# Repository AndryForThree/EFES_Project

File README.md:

# EFES_Project
Final Project for "Electronics for Embedded Systems" course of PoliTO 2026-2027. Automotive Steering System 

## File versionati e rigenerazione

Le regole sono commentate in `.gitignore`, `Firmware/.gitignore` e nel
`.gitignore` del firmware HumanSide.

- **KiCad:** schemi, PCB, progetti, regole e librerie (inclusi i modelli 3D).
  History locali, backup, lock, preferenze `.kicad_prl`, PDF e Gerber sono esclusi.
- **FreeCAD:** macro, script, JSON e documenti `.FCStd`; STEP/STL in `CAD/`
  e anteprime generate sono esclusi. Rigenerarli eseguendo le macro FreeCAD.
  I modelli in `PCB/CustomLibs/3D/` sono invece dipendenze del progetto KiCad.
- **Quartus/ModelSim:** HDL, testbench, script, `.qpf`, `.qsf`, IP e vincoli;
  database, prodotti di compilazione e simulazione sono esclusi.
- **STM32CubeMX/CMake:** `.ioc`, codice custom e configurazioni manuali;
  SDK, scaffolding rigenerabile e prodotti di build sono esclusi.
  Per HumanSide seguire `Firmware/EFES_FW_HumanSide/README.md`.
  Prima di compilare rigenerare anche font e asset con
  `python3 generate_font.py` in `Firmware/Scripts/FontGeneration/` e
  `python3 generate_assets.py` in `Firmware/Scripts/SymbolsGeneration/`.
- **Python:** sorgenti, test, configurazioni e dipendenze; ambienti virtuali,
  cache e prodotti di packaging sono esclusi.
- **LaTeX:** `.tex`, bibliografie e figure; file intermedi e PDF compilati
  dei report sono esclusi. Datasheet, riferimenti e allegati restano versionati.

I file ignorati restano disponibili sul disco ma non entrano nei commit.

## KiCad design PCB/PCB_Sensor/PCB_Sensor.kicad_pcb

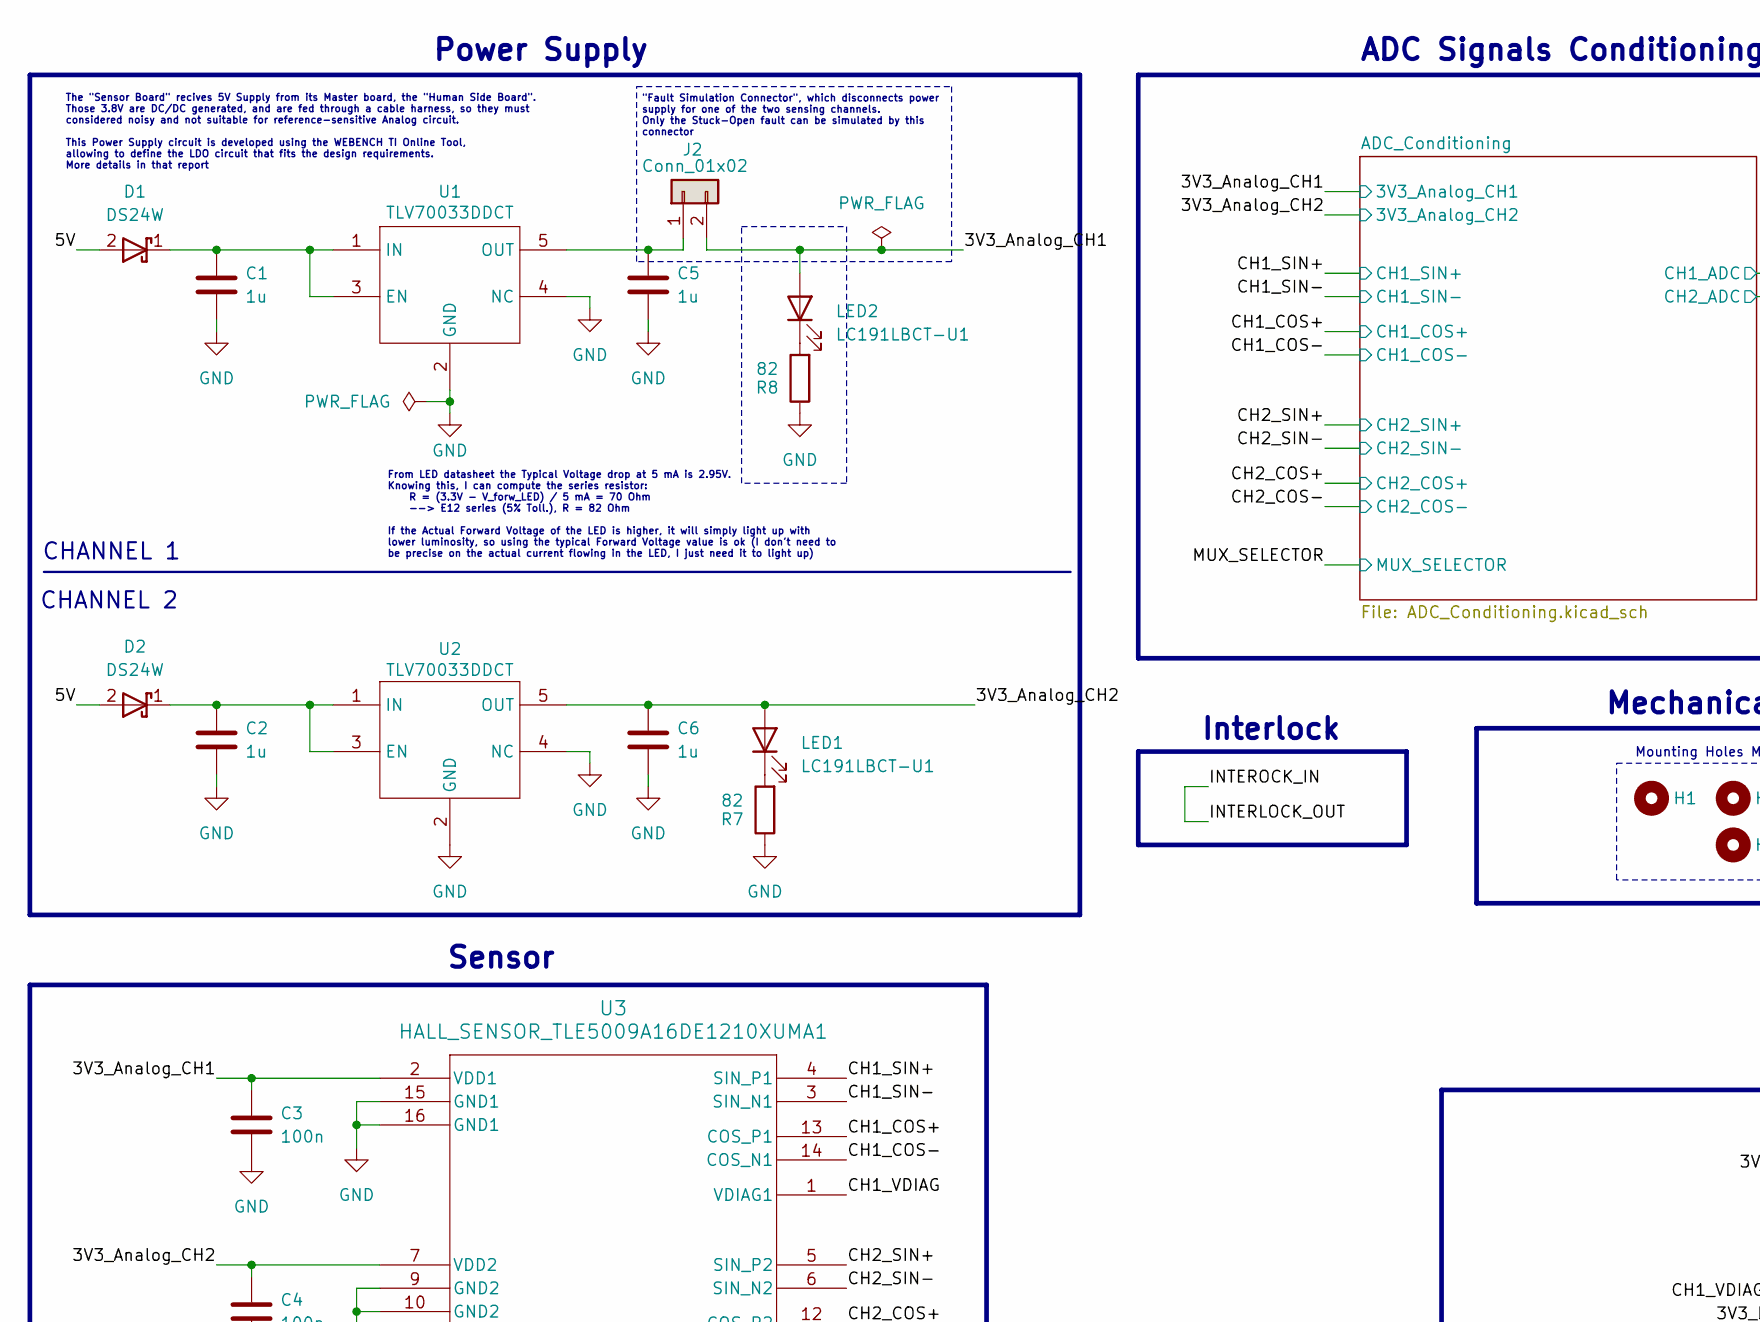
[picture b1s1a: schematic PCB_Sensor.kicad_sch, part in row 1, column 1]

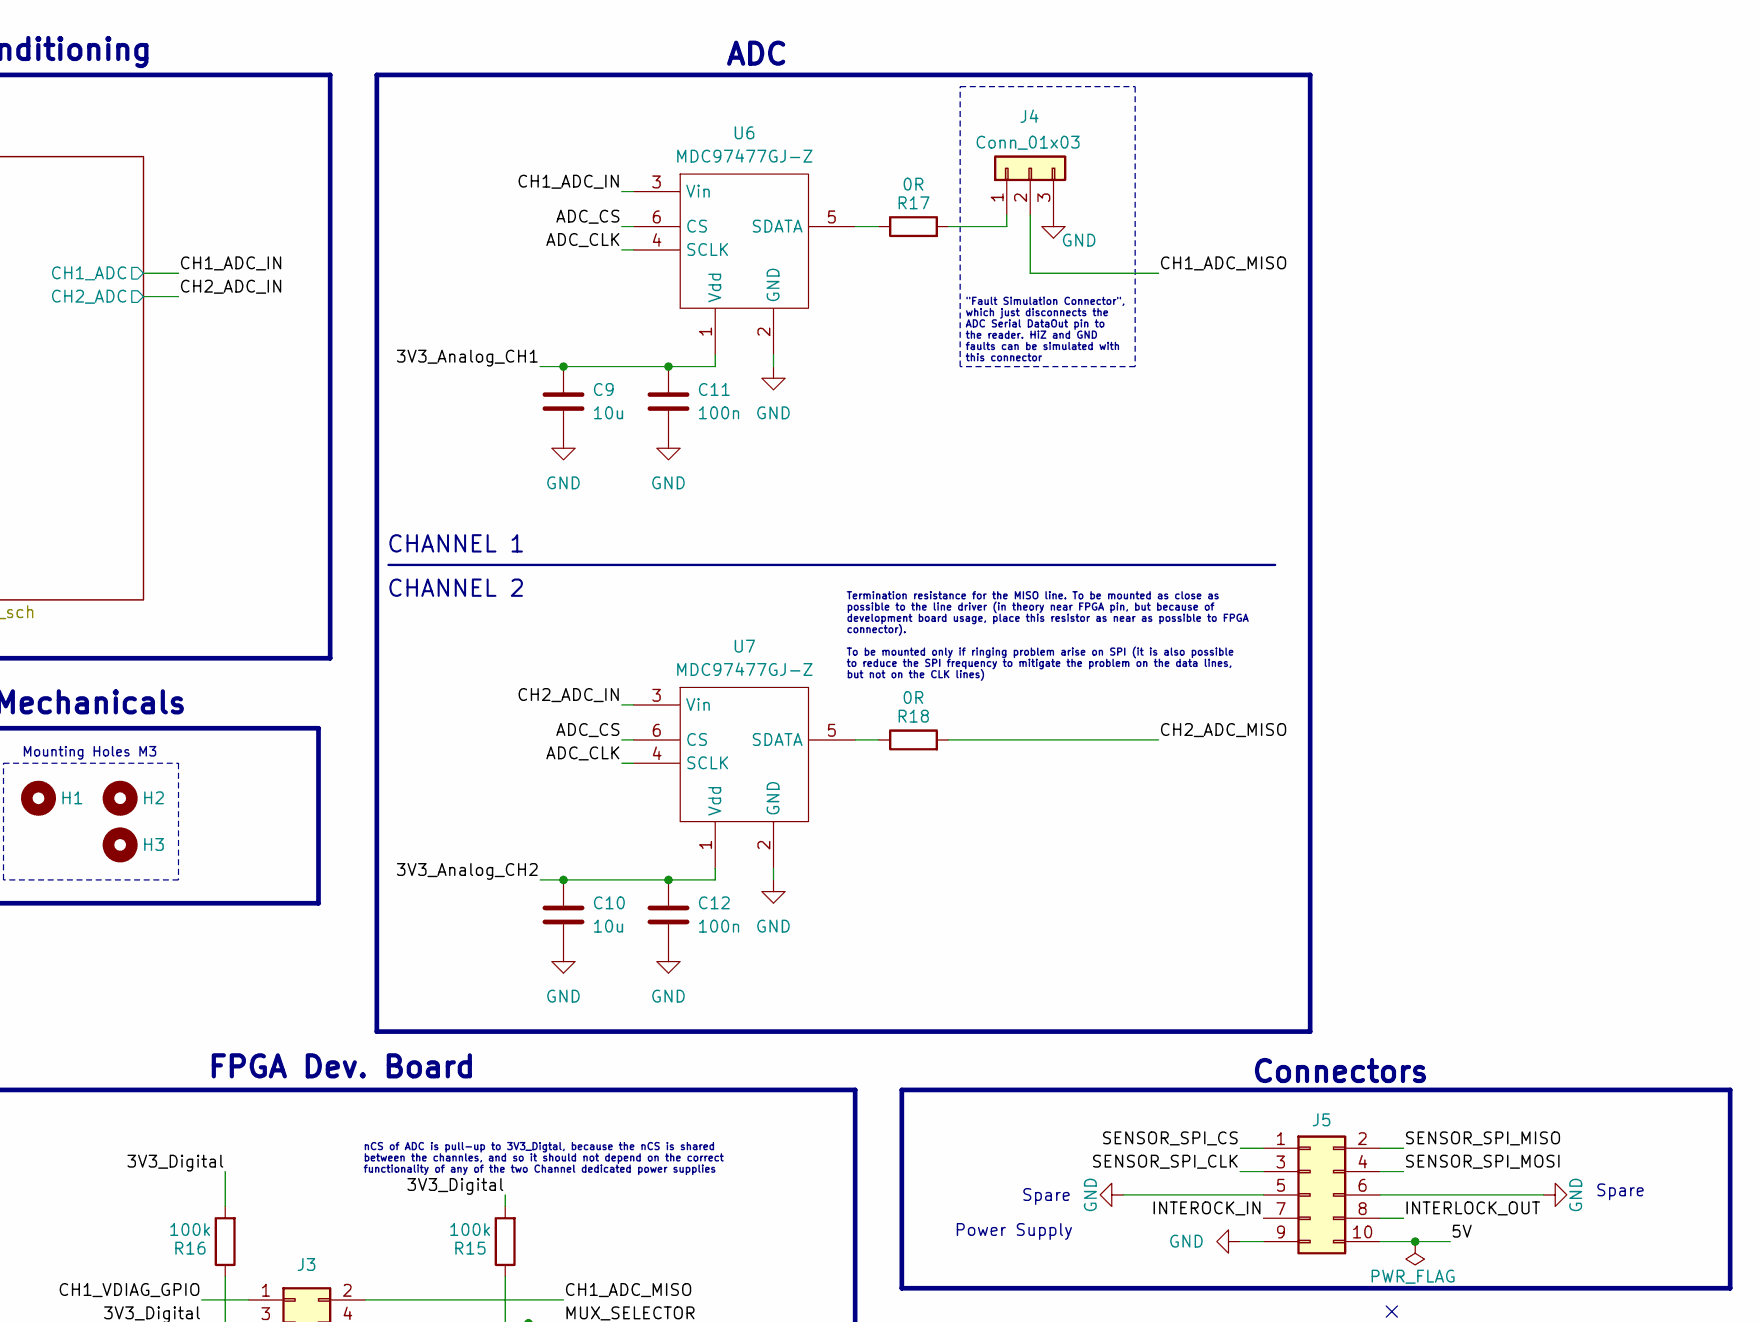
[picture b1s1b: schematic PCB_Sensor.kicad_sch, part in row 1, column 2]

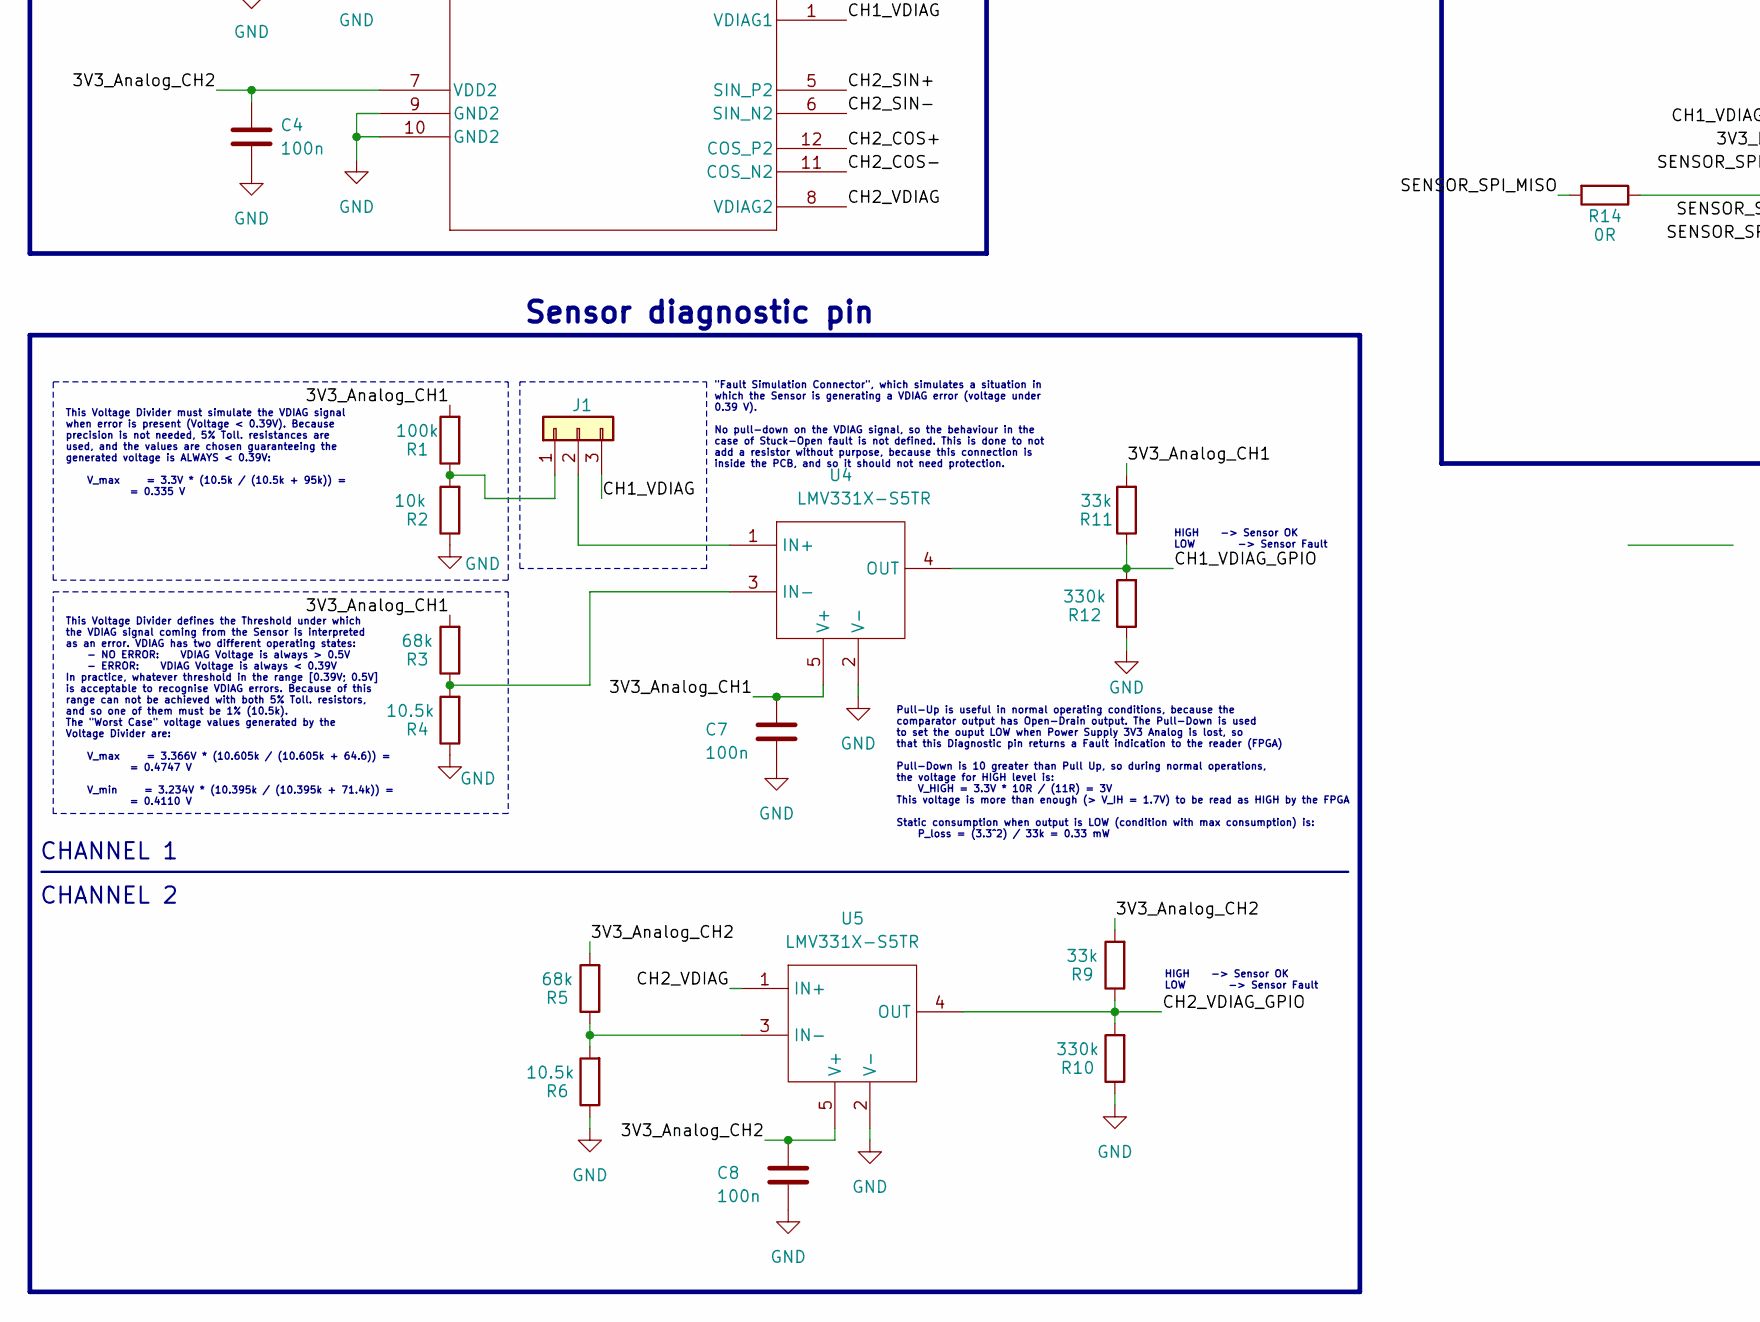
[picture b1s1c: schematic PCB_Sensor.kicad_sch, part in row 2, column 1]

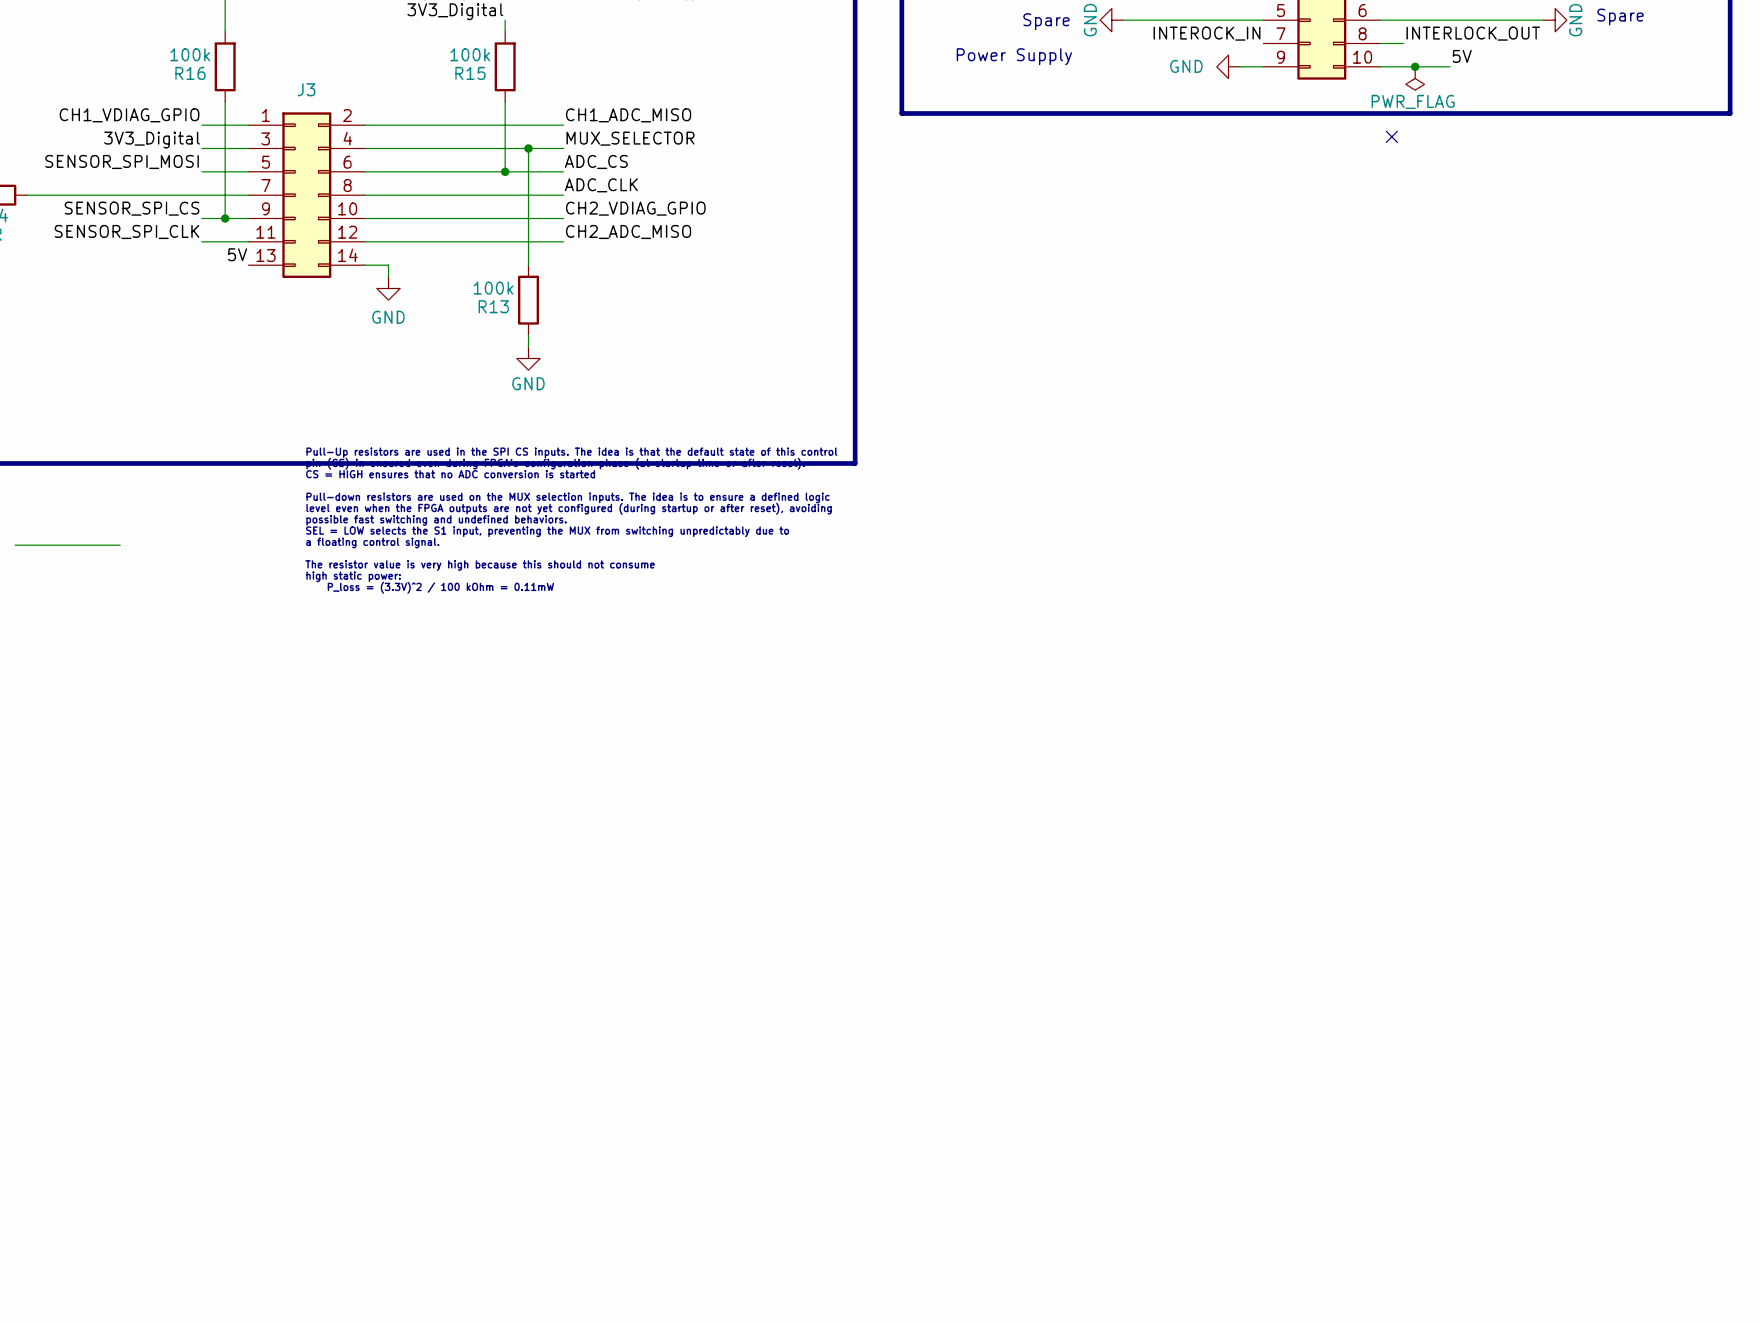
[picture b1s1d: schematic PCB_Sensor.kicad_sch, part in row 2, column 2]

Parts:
C1, C2, C5, C6: 1u; C_0805_2012Metric_Pad1.18x1.45mm_HandSolder
C3, C4, C7, C8, C11, C12: 100n; C_0805_2012Metric_Pad1.18x1.45mm_HandSolder
C9, C10: 10u; C_0805_2012Metric_Pad1.18x1.45mm_HandSolder
D1, D2: DS24W; SOD-123_HandSolder
H1, H2, H3: MountingHole; MountingHole_3.2mm_M3
J1, J4: Conn_01x03; PinHeader_1x03_P2.54mm_Vertical
J2: Conn_01x02; PinHeader_1x02_P2.54mm_Vertical
J3: SBH11-PBPC-D07-ST-BK; CONN_SBH11-PBPC-D07-ST-BK
J5: SBH11-PBPC-D05-RA-BK; CONN_SBH11-PBPC-D05-RA-BK
LED1, LED2: LC191LBCT-U1; LED_0603_HandSolder
R1, R13, R15, R16: 100k; R_0805_2012Metric_Pad1.20x1.40mm_HandSolder
R2: 10k; R_0805_2012Metric_Pad1.20x1.40mm_HandSolder
R3, R5: 68k; R_0805_2012Metric_Pad1.20x1.40mm_HandSolder
R4, R6: 10.5k; R_0805_2012Metric_Pad1.20x1.40mm_HandSolder
R7, R8: 82; R_0805_2012Metric_Pad1.20x1.40mm_HandSolder
R9, R11: 33k; R_0805_2012Metric_Pad1.20x1.40mm_HandSolder
R10, R12: 330k; R_0805_2012Metric_Pad1.20x1.40mm_HandSolder
R14, R17, R18: 0R; R_0805_2012Metric_Pad1.20x1.40mm_HandSolder
U1, U2: TLV70033DDCT; SOT-23-5
U3: HALL_SENSOR_TLE5009A16DE1210XUMA1
U4, U5: LMV331X-S5TR; SOT-23-5
U6, U7: MDC97477GJ-Z; SOT-23-6_DBV_TEX-M

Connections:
/3V3_Analog_CH1: C3.1, C7.1, C9.1, C11.1, J2.2, LED2.2 (A), R1.2, R3.2, R11.2, U3.2 (VDD1), U4.5 (V+), U6.1 (Vdd); also elsewhere on the board
/3V3_Analog_CH2: C4.1, C6.1, C8.1, C10.1, C12.1, LED1.2 (A), R5.2, R9.2, U2.5 (OUT), U3.7 (VDD2), U5.5 (V+), U7.1 (Vdd); also elsewhere on the board
/3V3_Digital: J3.3, R15.2, R16.2
/5V: D1.2 (A), D2.2 (A), J3.13 (Pin_9), J5.10
/ADC_CLK: J3.8, U6.4 (SCLK), U7.4 (SCLK)
/ADC_CS: J3.6, R15.1, U6.6 (CS), U7.6 (CS)
/CH1_ADC_IN: U6.3 (Vin); also elsewhere on the board
/CH1_ADC_MISO: J3.2, J4.2
/CH1_COS+: U3.13 (COS_P1); also elsewhere on the board
/CH1_COS-: U3.14 (COS_N1); also elsewhere on the board
/CH1_SIN+: U3.4 (SIN_P1); also elsewhere on the board
/CH1_SIN-: U3.3 (SIN_N1); also elsewhere on the board
/CH1_VDIAG: J1.3, U3.1 (VDIAG1)
/CH1_VDIAG_GPIO: J3.1, R11.1, R12.2, U4.4 (OUT)
/CH2_ADC_IN: U7.3 (Vin); also elsewhere on the board
/CH2_ADC_MISO: J3.12 (Pin_10), R18.2
/CH2_COS+: U3.12 (COS_P2); also elsewhere on the board
/CH2_COS-: U3.11 (COS_N2); also elsewhere on the board
/CH2_SIN+: U3.5 (SIN_P2); also elsewhere on the board
/CH2_SIN-: U3.6 (SIN_N2); also elsewhere on the board
/CH2_VDIAG: U3.8 (VDIAG2), U5.1 (IN+)
/CH2_VDIAG_GPIO: J3.10, R9.1, R10.2, U5.4 (OUT)
/INTERLOCK_OUT: J5.7, J5.8
/MUX_SELECTOR: J3.4, R13.2; also elsewhere on the board
/SENSOR_SPI_CLK: J3.11 (Pin_9), J5.3
/SENSOR_SPI_CS: J3.9, J5.1, R16.1
/SENSOR_SPI_MISO: J5.2, R14.2
/SENSOR_SPI_MOSI: J3.5, J5.4
GND: C1.2, C2.2, C3.2, C4.2, C5.2, C6.2, C7.2, C8.2, C9.2, C10.2, C11.2, C12.2, J3.14 (Pin_10), J4.3, J5.5, J5.6, J5.9, R2.1, R4.1, R6.1, R7.1, R8.1, R10.1, R12.1, R13.1, U1.2 (GND), U1.4 (NC), U2.2 (GND), U2.4 (NC), U3.9 (GND2), U3.10 (GND2), U3.15 (GND1), U3.16 (GND1), U4.2 (V-), U5.2 (V-), U6.2 (GND), U7.2 (GND); also elsewhere on the board
unnamed: C1.1, D1.1 (K), U1.1 (IN), U1.3 (EN)
unnamed: C2.1, D2.1 (K), U2.1 (IN), U2.3 (EN)
unnamed: J1.1, R1.1, R2.2
unnamed: J1.2, U4.1 (IN+)
unnamed: C5.1, J2.1, U1.5 (OUT)
unnamed: J3.7, R14.1
unnamed: J4.1, R17.2
unnamed: LED1.1 (K), R7.2
unnamed: LED2.1 (K), R8.2
unnamed: R3.1, R4.2, U4.3 (IN-)
unnamed: R5.1, R6.2, U5.3 (IN-)
unnamed: R17.1, U6.5 (SDATA)
unnamed: R18.1, U7.5 (SDATA)

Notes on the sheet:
CHANNEL 2
CHANNEL 1
From LED datasheet the Typical Voltage drop at 5 mA is 2.95V. Knowing this, I can compute the series resistor: R = (3.3V - V_forw_LED) / 5 mA = 70 Ohm --> E12 series (5% Toll.), R = 82 Ohm If the Actual Forward Voltage of the LED is higher, it will simply light up with lower luminosity, so using th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
Spare
Pull-Up is useful in normal operating conditions, because the comparator output has Open-Drain output. The Pull-Down is used to set the ouput LOW when Power Supply 3V3 Analog is lost, so that this Diagnostic pin returns a Fault indication to the reader (FPGA) Pull-Down is 10 greater than Pull Up, s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
Connectors
"Fault Simulation Connector", which just disconnects the ADC Serial DataOut pin to the reader. HiZ and GND faults can be simulated with this connector
nCS of ADC is pull-up to 3V3_Digtal, because the nCS is shared between the channles, and so it should not depend on the correct functionality of any of the two Channel dedicated power supplies
Sensor diagnostic pin
FPGA Dev. Board
HIGH -> Sensor OK LOW -> Sensor Fault
Mechanicals
Power Supply
ADC Signals Conditioning
This Voltage Divider defines the Threshold under which the VDIAG signal coming from the Sensor is interpreted as an error. VDIAG has two different operating states: - NO ERROR: VDIAG Voltage is always > 0.5V - ERROR: VDIAG Voltage is always < 0.39V In practice, whatever threshold in the range [0.39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
Mounting Holes M3
"Fault Simulation Connector", which simulates a situation in which the Sensor is generating a VDIAG error (voltage under 0.39 V). No pull-down on the VDIAG signal, so the behaviour in the case of Stuck-Open fault is not defined. This is done to not add a resistor without purpose, because this conne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
"Fault Simulation Connector", which disconnects power supply for one of the two sensing channels. Only the Stuck-Open fault can be simulated by this connector
Pull-Up resistors are used in the SPI CS inputs. The idea is that the default state of this control pin (CS) in ensured even during FPGA's configuration phase (at startup time or after reset). CS = HIGH ensures that no ADC conversion is started Pull-down resistors are used on the MUX selection inpu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
Interlock
Termination resistance for the MISO line. To be mounted as close as possible to the line driver (in theory near FPGA pin, but because of development board usage, place this resistor as near as possible to FPGA connector). To be mounted only if ringing problem arise on SPI (it is also possible to re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
Sensor
This Voltage Divider must simulate the VDIAG signal when error is present (Voltage < 0.39V). Because precision is not needed, 5% Toll. resistances are used, and the values are chosen guaranteeing the generated voltage is ALWAYS < 0.39V: V_max = 3.3V * (10.5k / (10.5k + 95k)) = = 0.335 V
ADC
The "Sensor Board" recives 5V Supply from its Master board, the "Human Side Board". Those 3.8V are DC/DC generated, and are fed through a cable harness, so they must considered noisy and not suitable for reference-sensitive Analog circuit. This Power Supply circuit is developed using the WEBENCH TI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

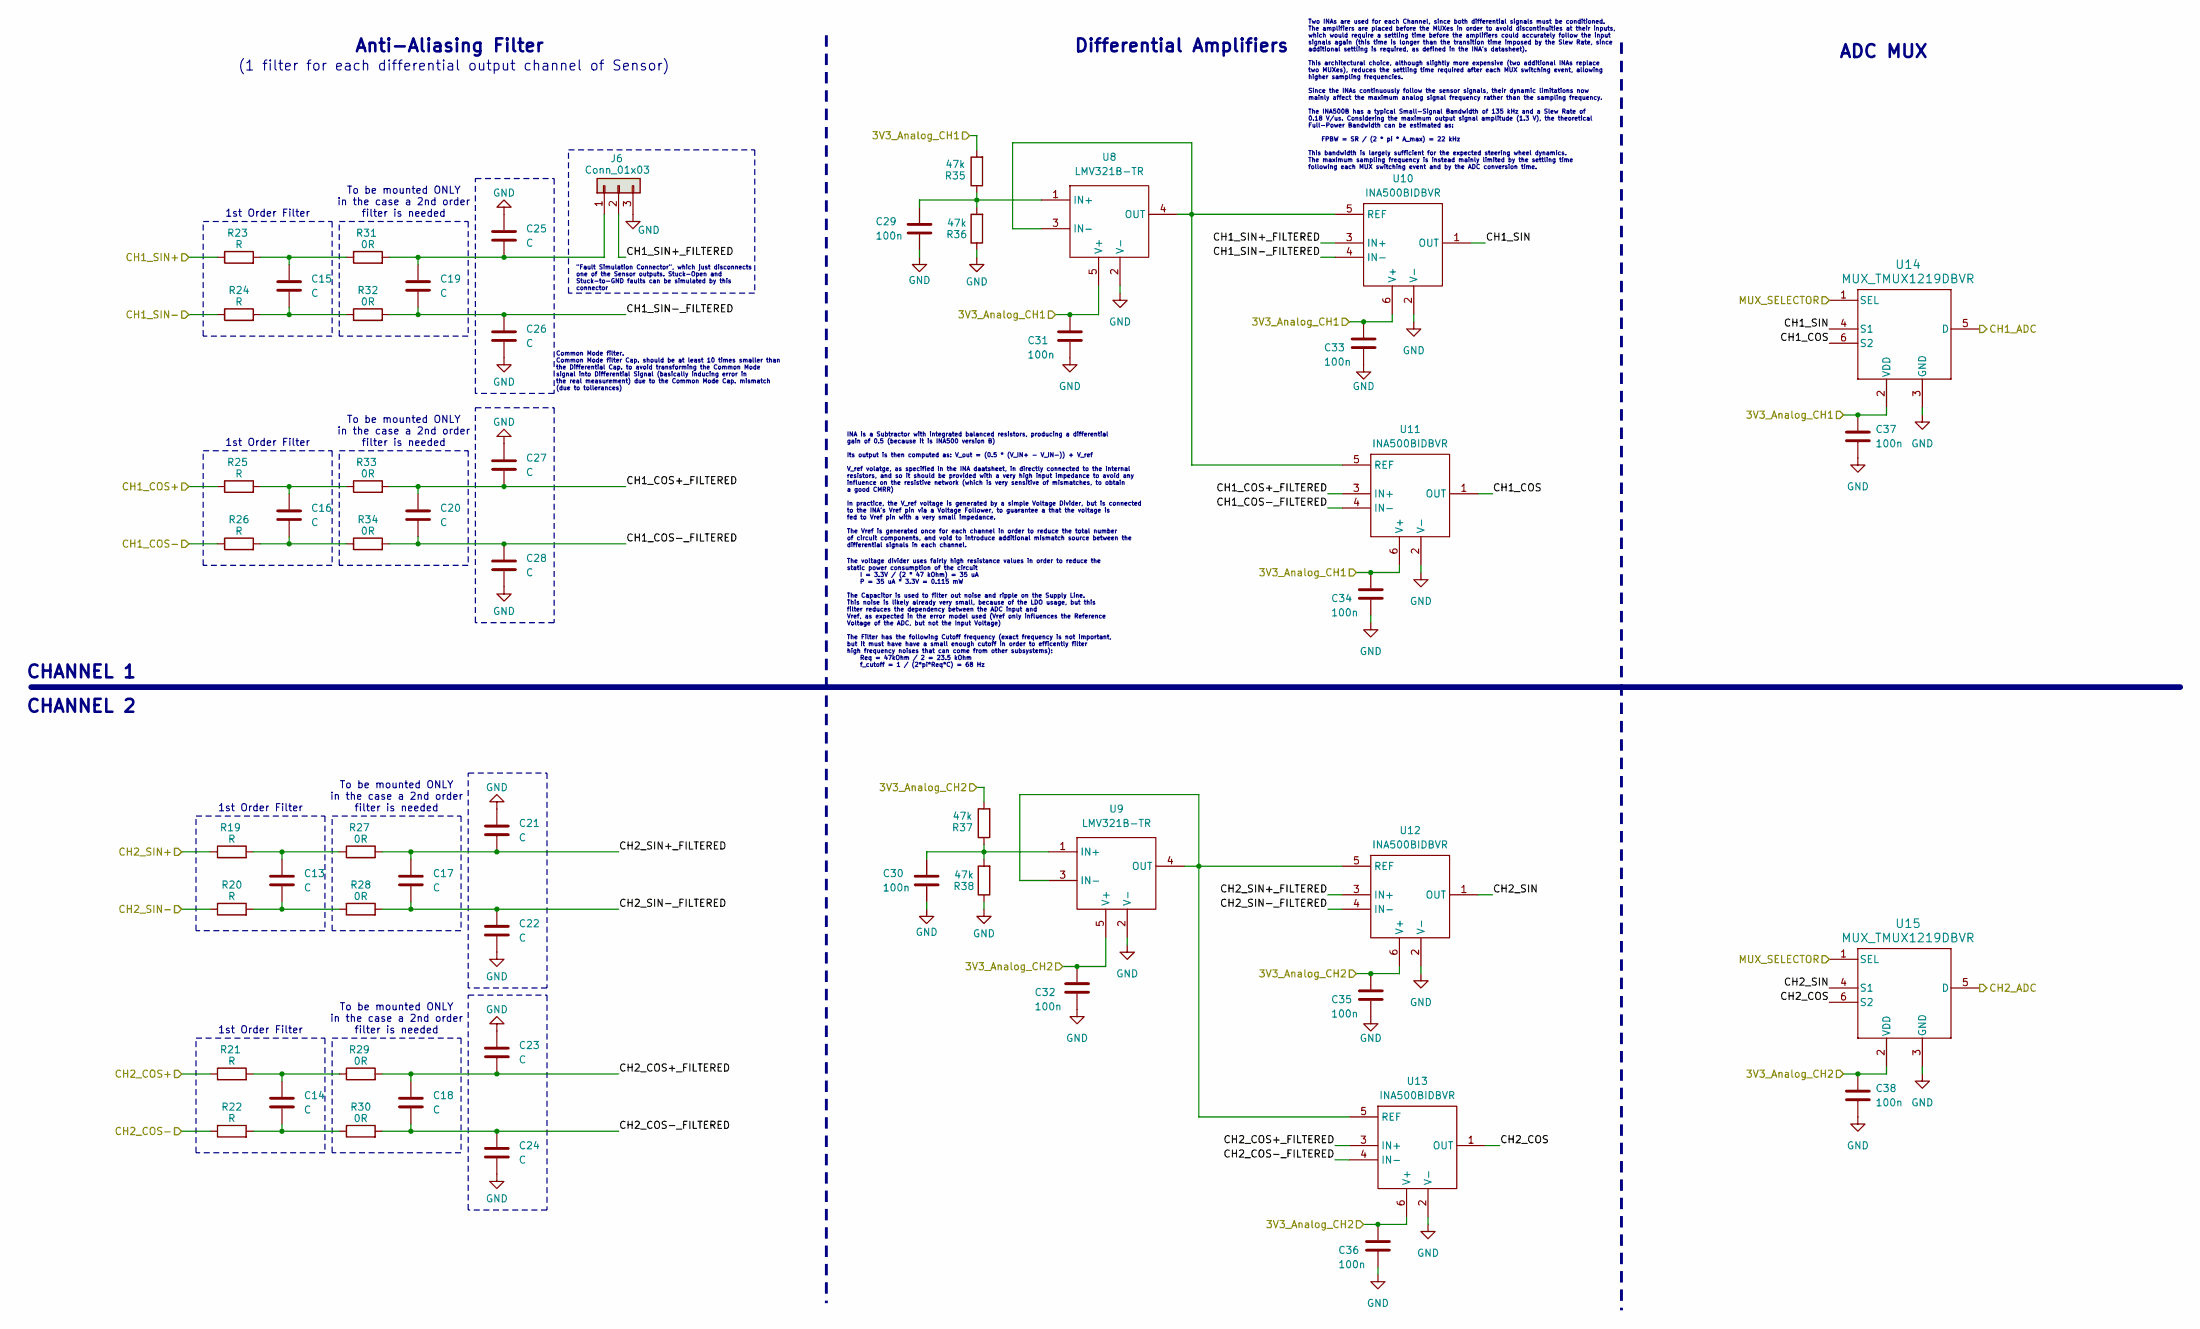
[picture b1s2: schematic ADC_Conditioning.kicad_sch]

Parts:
C13, C14, C15, C16, C17, C18, C19, C20, C21, C22, C23, C24, C25, C26, C27, C28: C; C_0805_2012Metric_Pad1.18x1.45mm_HandSolder
C29, C30, C31, C32, C33, C34, C35, C36, C37, C38: 100n; C_0805_2012Metric_Pad1.18x1.45mm_HandSolder
J6: Conn_01x03; PinHeader_1x03_P2.54mm_Vertical
R19, R20, R21, R22, R23, R24, R25, R26: R; R_0805_2012Metric_Pad1.20x1.40mm_HandSolder
R27, R28, R29, R30, R31, R32, R33, R34: 0R; R_0805_2012Metric_Pad1.20x1.40mm_HandSolder
R35, R36, R37, R38: 47k; R_0805_2012Metric_Pad1.20x1.40mm_HandSolder
U8, U9: LMV321B-TR; SOT-23-5
U10, U11, U12, U13: INA500BIDBVR; SOT-23-6_DBV_TEX-M
U14, U15: MUX_TMUX1219DBVR; SOT-23-6_DBV_TEX-M

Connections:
/3V3_Analog_CH1: C31.1, C33.1, C34.1, C37.1, R35.2, U8.5 (V+), U10.6 (V+), U11.6 (V+), U14.2 (VDD); also elsewhere on the board
/3V3_Analog_CH2: C32.1, C35.1, C36.1, C38.1, R37.2, U9.5 (V+), U12.6 (V+), U13.6 (V+), U15.2 (VDD); also elsewhere on the board
/ADC_Conditioning/CH1_COS: U11.1 (OUT), U14.6 (S2)
/ADC_Conditioning/CH1_COS+_FILTERED: C20.1, C27.2, R33.2, U11.3 (IN+)
/ADC_Conditioning/CH1_COS-_FILTERED: C20.2, C28.1, R34.2, U11.4 (IN-)
/ADC_Conditioning/CH1_SIN: U10.1 (OUT), U14.4 (S1)
/ADC_Conditioning/CH1_SIN+_FILTERED: J6.2, U10.3 (IN+)
/ADC_Conditioning/CH1_SIN-_FILTERED: C19.2, C26.1, R32.2, U10.4 (IN-)
/ADC_Conditioning/CH2_COS: U13.1 (OUT), U15.6 (S2)
/ADC_Conditioning/CH2_COS+_FILTERED: C18.1, C23.2, R29.2, U13.3 (IN+)
/ADC_Conditioning/CH2_COS-_FILTERED: C18.2, C24.1, R30.2, U13.4 (IN-)
/ADC_Conditioning/CH2_SIN: U12.1 (OUT), U15.4 (S1)
/ADC_Conditioning/CH2_SIN+_FILTERED: C17.1, C21.2, R27.2, U12.3 (IN+)
/ADC_Conditioning/CH2_SIN-_FILTERED: C17.2, C22.1, R28.2, U12.4 (IN-)
/CH1_ADC_IN: U14.5 (D); also elsewhere on the board
/CH1_COS+: R25.1; also elsewhere on the board
/CH1_COS-: R26.1; also elsewhere on the board
/CH1_SIN+: R23.1; also elsewhere on the board
/CH1_SIN-: R24.1; also elsewhere on the board
/CH2_ADC_IN: U15.5 (D); also elsewhere on the board
/CH2_COS+: R21.1; also elsewhere on the board
/CH2_COS-: R22.1; also elsewhere on the board
/CH2_SIN+: R19.1; also elsewhere on the board
/CH2_SIN-: R20.1; also elsewhere on the board
/MUX_SELECTOR: U14.1 (SEL), U15.1 (SEL); also elsewhere on the board
GND: C21.1, C22.2, C23.1, C24.2, C25.1, C26.2, C27.1, C28.2, C29.2, C30.2, C31.2, C32.2, C33.2, C34.2, C35.2, C36.2, C37.2, C38.2, J6.3, R36.1, R38.1, U8.2 (V-), U9.2 (V-), U10.2 (V-), U11.2 (V-), U12.2 (V-), U13.2 (V-), U14.3 (GND), U15.3 (GND); also elsewhere on the board
unnamed: C13.1, R19.2, R27.1
unnamed: C13.2, R20.2, R28.1
unnamed: C14.1, R21.2, R29.1
unnamed: C14.2, R22.2, R30.1
unnamed: C15.1, R23.2, R31.1
unnamed: C15.2, R24.2, R32.1
unnamed: C16.1, R25.2, R33.1
unnamed: C16.2, R26.2, R34.1
unnamed: C19.1, C25.2, J6.1, R31.2
unnamed: C29.1, R35.1, R36.2, U8.1 (IN+)
unnamed: C30.1, R37.1, R38.2, U9.1 (IN+)
unnamed: U8.3 (IN-), U8.4 (OUT), U10.5 (REF), U11.5 (REF)
unnamed: U9.3 (IN-), U9.4 (OUT), U12.5 (REF), U13.5 (REF)

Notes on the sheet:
"Fault Simulation Connector", which just disconnects one of the Sensor outputs. Stuck-Open and Stuck-to-GND faults can be simulated by this connector
To be mounted ONLY in the case a 2nd order filter is needed
CHANNEL 2
Two INAs are used for each Channel, since both differential signals must be conditioned. The amplifiers are placed before the MUXes in order to avoid discontinuities at their inputs, which would require a settling time before the amplifiers could accurately follow the input signals again (this time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
1st Order Filter
Differential Amplifiers
The voltage divider uses fairly high resistance values in order to reduce the static power consumption of the circuit I = 3.3V / (2 * 47 kOhm) = 35 uA P = 35 uA * 3.3V = 0.115 mW The Capacitor is used to filter out noise and ripple on the Supply Line. This noise is likely already very small, becaus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
ADC MUX
INA is a Subtractor with integrated balanced resistors, producing a differential gain of 0.5 (because it is INA500 version B) Its output is then computed as: V_out = (0.5 * (V_IN+ - V_IN-)) + V_ref V_ref volatge, as specified in the INA daatsheet, in directly connected to the internal resistors, an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
(1 filter for each differential output channel of Sensor)
Common Mode filter. Common Mode filter Cap. should be at least 10 times smaller than the Differential Cap. to avoid transforming the Common Mode signal into Differential Signal (basically inducing error in the real measurement) due to the Common Mode Cap. mismatch (due to tollerances)
CHANNEL 1
Anti-Aliasing Filter

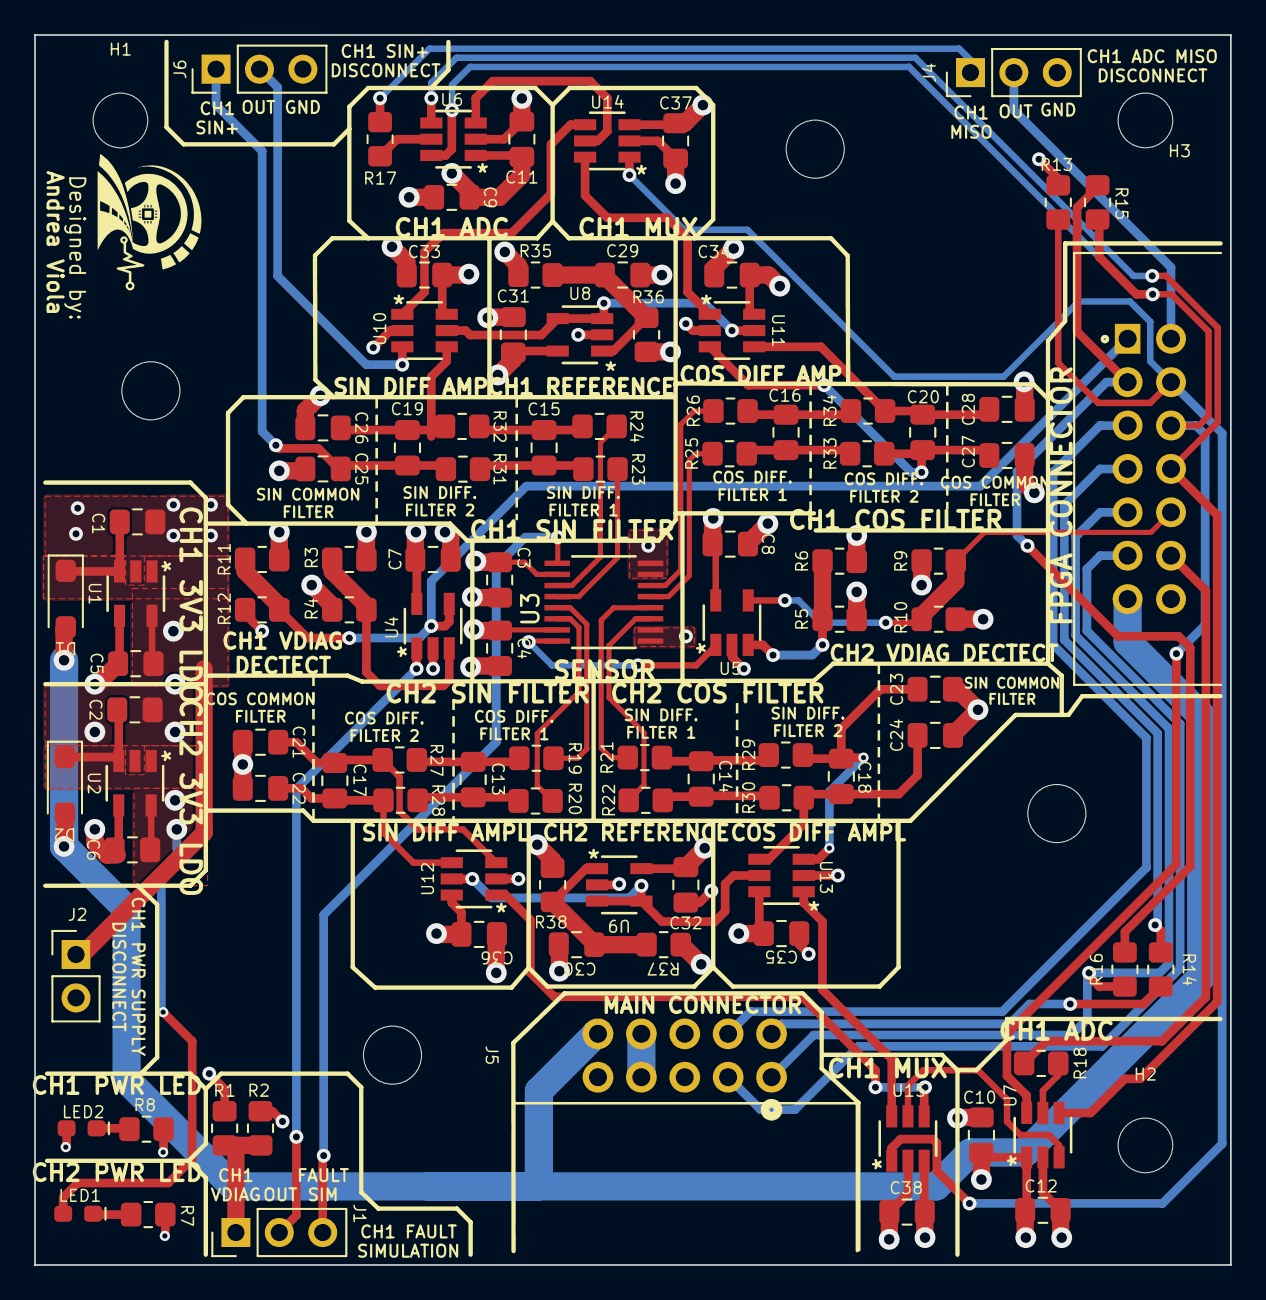
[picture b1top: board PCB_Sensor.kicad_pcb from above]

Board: 4 copper layers, 70.0 x 72.0 mm, 104 parts (0 on the bottom side), 67 nets.
